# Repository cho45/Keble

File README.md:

# Keble
My Keyboard project

![keyboard]( https://lh3.googleusercontent.com/EfxbqDVbFUMFygQ37cw-t-osZh-F7l7Be6ySQvdsSEX0ixMYkyIdGHLsxJQ2jPK_8Zz_0KA0nsUGFINB1TGCXRP6lfS0WsB-HddwQOFWCWsFthSKxl6NGZ9FwDPpazG6D0C-81J806JqIFrc-be6p1uPMkH3qnAab_ow4JNFFRUdB4O2-49kGolg-Dy7JXoRlwxNpvhNOfnoP4gZtVEllJxjIrvzIPy5hKqrV-IkeFJhrkAK_e5a8ZNKsllVUzNcYYQIi22m2K5YhwaDDLRgU-2dTrrQqDLFtFhZ6oY2y8DjeTC2zXfAGccmpLrrazCjzrdYzKibt8z4t2GqVdgDhCtJQ7x6MYJDr5eFAhxukxrMP_dcSZdACXUI4Rjq47IPYyl1GPYx97pCoO8hBt4gX-3HaJTRLynqYn73mz2nr6UBCkSG0HlI_O6zHuUVOPiS8QQIJsX-bBW7ScQR7BRKUgOtjzX-zlCG5ynrySV1wSH0WuWNiJt9iEEp95V1wKW2NQUl0bESZkWuitu_E9rONg5-YWEImFMoQkPSbXobiScAQ6pdmA8vURFWd6wHuSsA_RqvVRxijmWQiCGAefmiXdKXR_iKclWGiZpoRNCDzVIgeSu1jw=w1756-h748-no )

## Schematic/PCB Project

This is KiCAD project.

Open Root.sch for viewing overall schematic.

## Using Hardwares

 * BLE Nano (nRF51288)
 * MCP23017 (I2C GPIO)
 * Gateron Switches (Cherry MX compatible)

## Firmware

https://developer.mbed.org/users/cho45/code/keyboard/

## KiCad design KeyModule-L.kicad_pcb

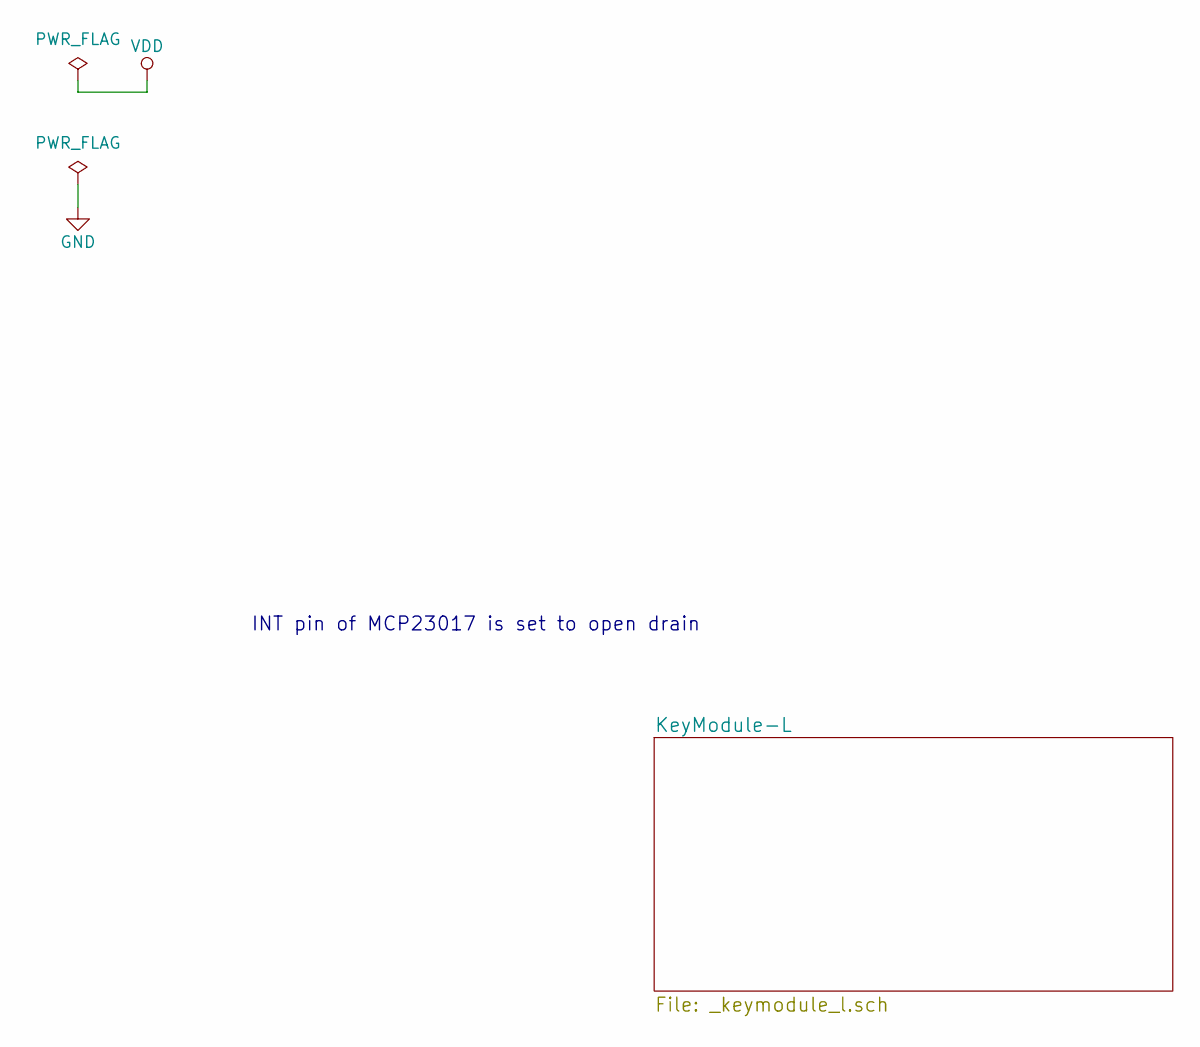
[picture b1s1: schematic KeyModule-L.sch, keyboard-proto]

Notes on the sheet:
INT pin of MCP23017 is set to open drain

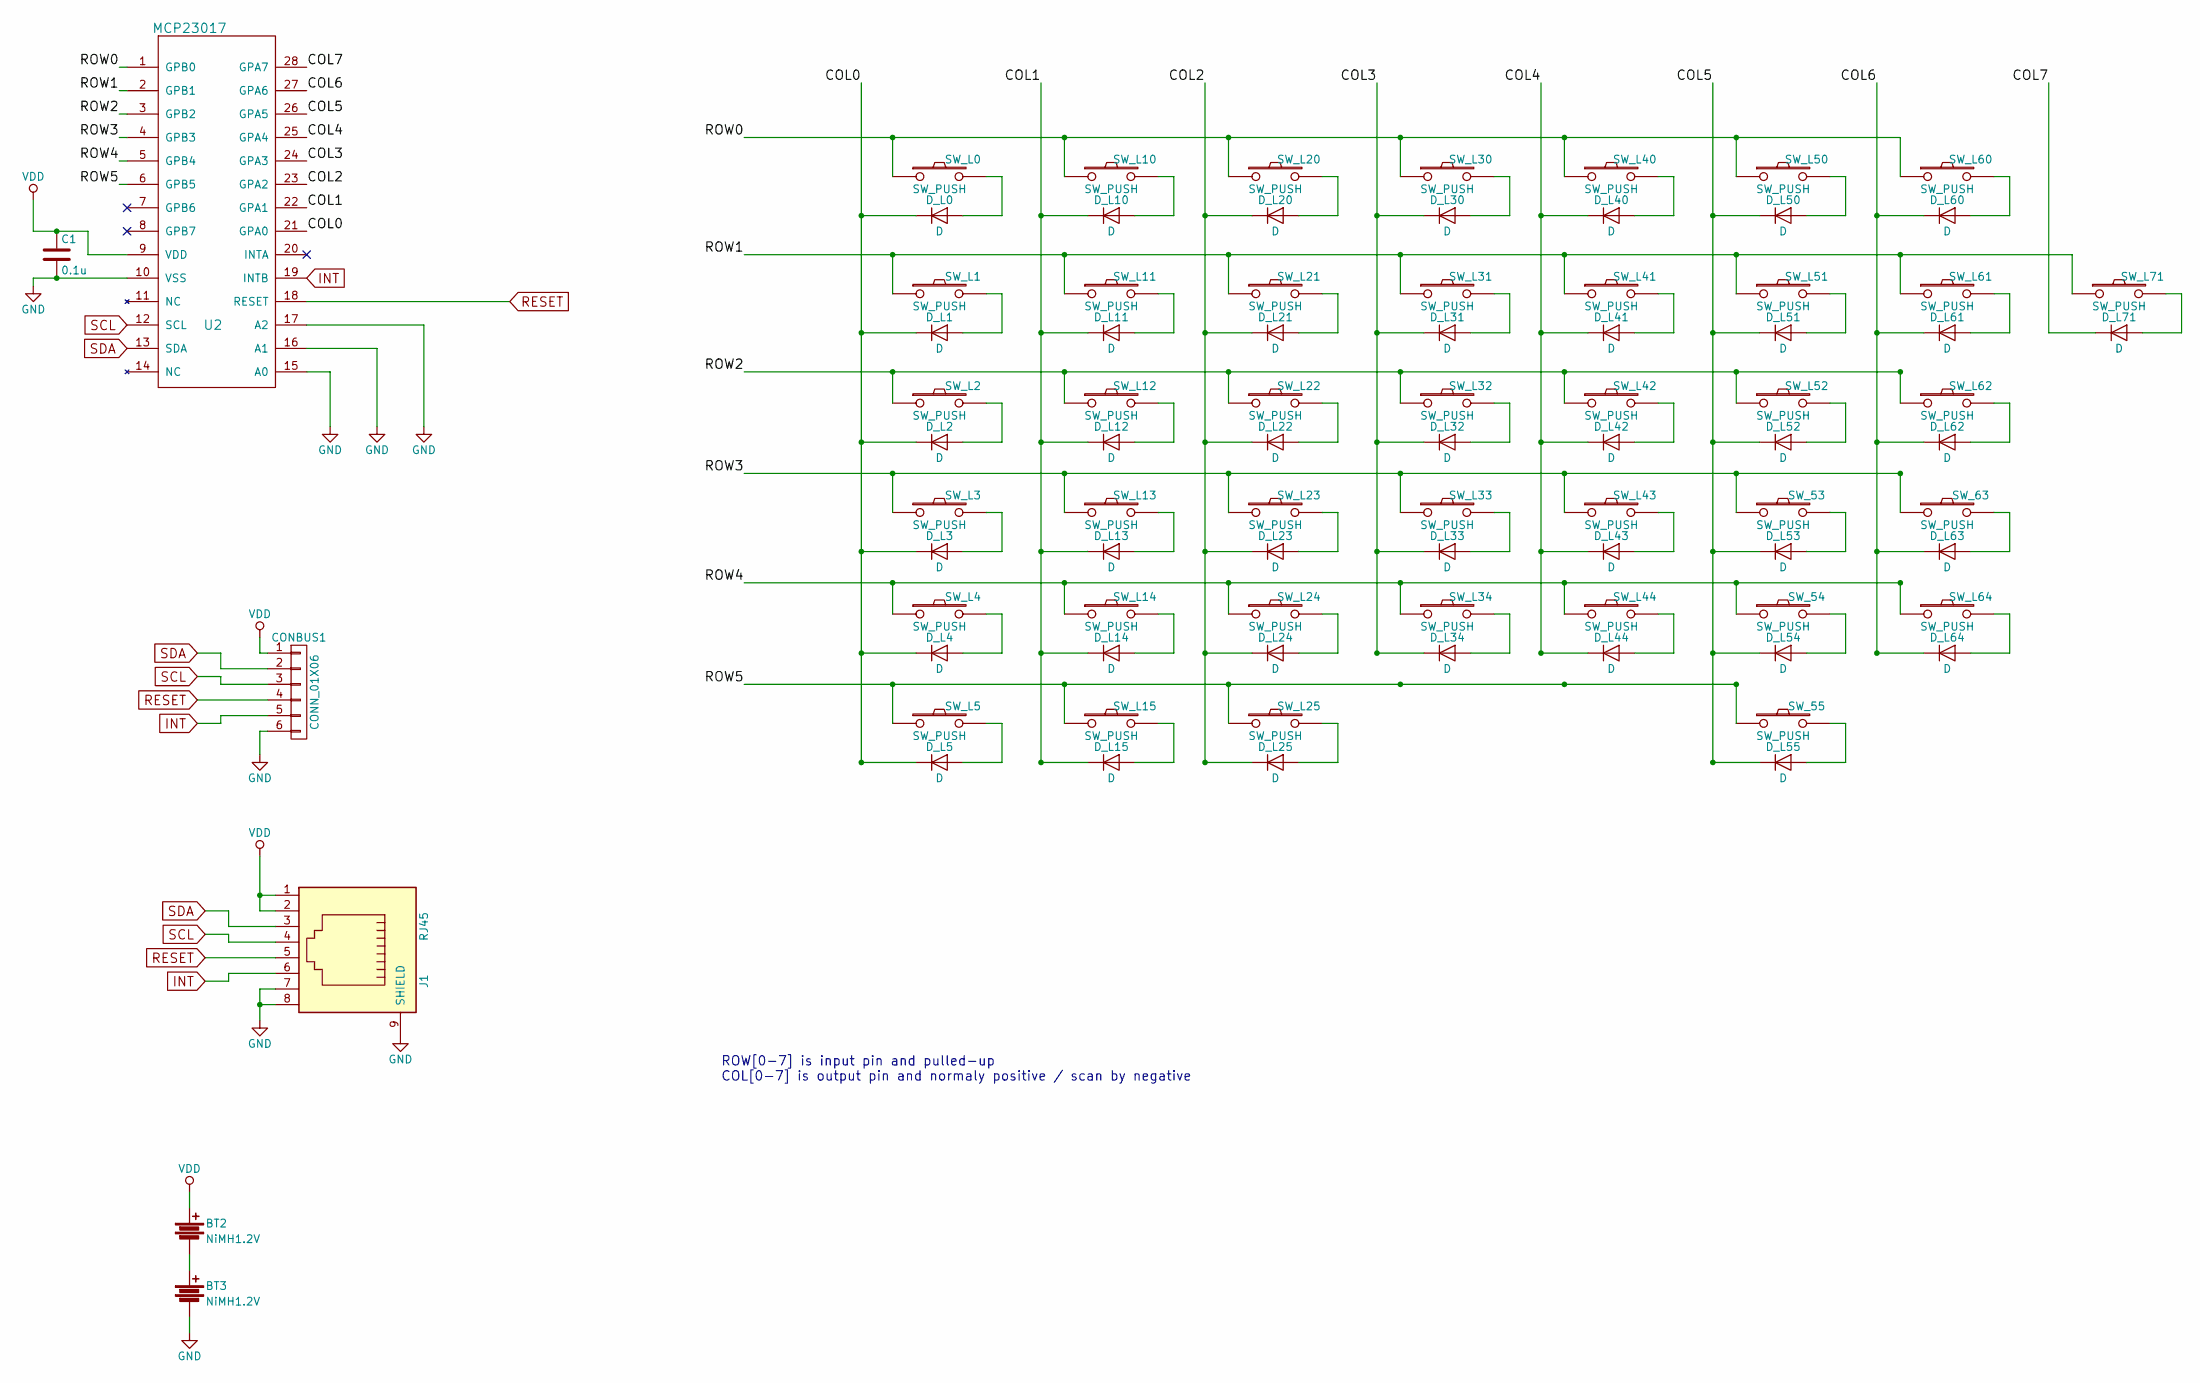
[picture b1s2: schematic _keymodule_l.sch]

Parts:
BT2, BT3: NiMH1.2V; BAT-P-00308
C1: 0.1u; C_Rect_L4_W2.5_P2.5
CONBUS1: CONN_01X06; Socket_Strip_Straight_1x06
D_L0, D_L1, D_L2, D_L3, D_L4, D_L5, D_L10, D_L11, D_L12, D_L13, D_L14, D_L15, D_L20, D_L21, D_L22, D_L23, D_L24, D_L25, D_L30, D_L31, D_L32, D_L33, D_L34, D_L40, D_L41, D_L42, D_L43, D_L44, D_L50, D_L51, D_L52, D_L53, D_L54, D_L55, D_L60, D_L61, D_L62, D_L63, D_L64, D_L71: D; Diode_DO-35_SOD27_Horizontal_RM10
J1: RJ45; RJ45-7810-XPXC
SW_53, SW_54, SW_55, SW_63: SW_PUSH; MX1A
SW_L0, SW_L1, SW_L2, SW_L3, SW_L4, SW_L5, SW_L10, SW_L11, SW_L12, SW_L13, SW_L14, SW_L15, SW_L20, SW_L21, SW_L22, SW_L23, SW_L24, SW_L25, SW_L30, SW_L31, SW_L32, SW_L33, SW_L34, SW_L40, SW_L41, SW_L42, SW_L43, SW_L44, SW_L50, SW_L51, SW_L52, SW_L60, SW_L61, SW_L62, SW_L64, SW_L71: SW_PUSH; MX1A
U3: MCP23017; DIP-28_W7.62mm_LongPads

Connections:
/KeyModule-L/COL0: D_L0.1 (K), D_L1.1 (K), D_L2.1 (K), D_L3.1 (K), D_L4.1 (K), D_L5.1 (K); also elsewhere on the board
/KeyModule-L/COL1: D_L10.1 (K), D_L11.1 (K), D_L12.1 (K), D_L13.1 (K), D_L14.1 (K), D_L15.1 (K); also elsewhere on the board
/KeyModule-L/COL2: D_L20.1 (K), D_L21.1 (K), D_L22.1 (K), D_L23.1 (K), D_L24.1 (K), D_L25.1 (K); also elsewhere on the board
/KeyModule-L/COL3: D_L30.1 (K), D_L31.1 (K), D_L32.1 (K), D_L33.1 (K), D_L34.1 (K); also elsewhere on the board
/KeyModule-L/COL4: D_L40.1 (K), D_L41.1 (K), D_L42.1 (K), D_L43.1 (K), D_L44.1 (K); also elsewhere on the board
/KeyModule-L/COL5: D_L50.1 (K), D_L51.1 (K), D_L52.1 (K), D_L53.1 (K), D_L54.1 (K), D_L55.1 (K); also elsewhere on the board
/KeyModule-L/COL6: D_L60.1 (K), D_L61.1 (K), D_L62.1 (K), D_L63.1 (K), D_L64.1 (K); also elsewhere on the board
/KeyModule-L/COL7: D_L71.1 (K); also elsewhere on the board
/KeyModule-L/ROW0: SW_L0.1, SW_L10.1, SW_L20.1, SW_L30.1, SW_L40.1, SW_L50.1, SW_L60.1; also elsewhere on the board
/KeyModule-L/ROW1: SW_L1.1, SW_L11.1, SW_L21.1, SW_L31.1, SW_L41.1, SW_L51.1, SW_L61.1, SW_L71.1; also elsewhere on the board
/KeyModule-L/ROW2: SW_L2.1, SW_L12.1, SW_L22.1, SW_L32.1, SW_L42.1, SW_L52.1, SW_L62.1; also elsewhere on the board
/KeyModule-L/ROW3: SW_53.1, SW_63.1, SW_L3.1, SW_L13.1, SW_L23.1, SW_L33.1, SW_L43.1; also elsewhere on the board
/KeyModule-L/ROW4: SW_54.1, SW_L4.1, SW_L14.1, SW_L24.1, SW_L34.1, SW_L44.1, SW_L64.1; also elsewhere on the board
/KeyModule-L/ROW5: SW_55.1, SW_L5.1, SW_L15.1, SW_L25.1; also elsewhere on the board
GND: BT3.2, C1.2, CONBUS1.6, J1.7, J1.8, J1.9 (SHIELD); also elsewhere on the board
INT: CONBUS1.5, J1.6; also elsewhere on the board
unnamed: BT2.2, BT3.1
unnamed: D_L0.2 (A), SW_L0.2
unnamed: D_L1.2 (A), SW_L1.2
unnamed: D_L2.2 (A), SW_L2.2
unnamed: D_L3.2 (A), SW_L3.2
unnamed: D_L4.2 (A), SW_L4.2
unnamed: D_L5.2 (A), SW_L5.2
unnamed: D_L10.2 (A), SW_L10.2
unnamed: D_L11.2 (A), SW_L11.2
unnamed: D_L12.2 (A), SW_L12.2
unnamed: D_L13.2 (A), SW_L13.2
unnamed: D_L14.2 (A), SW_L14.2
unnamed: D_L15.2 (A), SW_L15.2
unnamed: D_L20.2 (A), SW_L20.2
unnamed: D_L21.2 (A), SW_L21.2
unnamed: D_L22.2 (A), SW_L22.2
unnamed: D_L23.2 (A), SW_L23.2
unnamed: D_L24.2 (A), SW_L24.2
unnamed: D_L25.2 (A), SW_L25.2
unnamed: D_L30.2 (A), SW_L30.2
unnamed: D_L31.2 (A), SW_L31.2
unnamed: D_L32.2 (A), SW_L32.2
unnamed: D_L33.2 (A), SW_L33.2
unnamed: D_L34.2 (A), SW_L34.2
unnamed: D_L40.2 (A), SW_L40.2
unnamed: D_L41.2 (A), SW_L41.2
unnamed: D_L42.2 (A), SW_L42.2
unnamed: D_L43.2 (A), SW_L43.2
unnamed: D_L44.2 (A), SW_L44.2
unnamed: D_L50.2 (A), SW_L50.2
unnamed: D_L51.2 (A), SW_L51.2
unnamed: D_L52.2 (A), SW_L52.2
unnamed: D_L53.2 (A), SW_53.2
unnamed: D_L54.2 (A), SW_54.2
unnamed: D_L55.2 (A), SW_55.2
unnamed: D_L60.2 (A), SW_L60.2
unnamed: D_L61.2 (A), SW_L61.2
unnamed: D_L62.2 (A), SW_L62.2
unnamed: D_L63.2 (A), SW_63.2
unnamed: D_L64.2 (A), SW_L64.2
unnamed: D_L71.2 (A), SW_L71.2
RESET: CONBUS1.4, J1.5; also elsewhere on the board
SCL: CONBUS1.3, J1.4; also elsewhere on the board
SDA: CONBUS1.2, J1.3; also elsewhere on the board
VDD: BT2.1, C1.1, CONBUS1.1, J1.1, J1.2; also elsewhere on the board

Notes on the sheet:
ROW[0-7] is input pin and pulled-up COL[0-7] is output pin and normaly positive / scan by negative

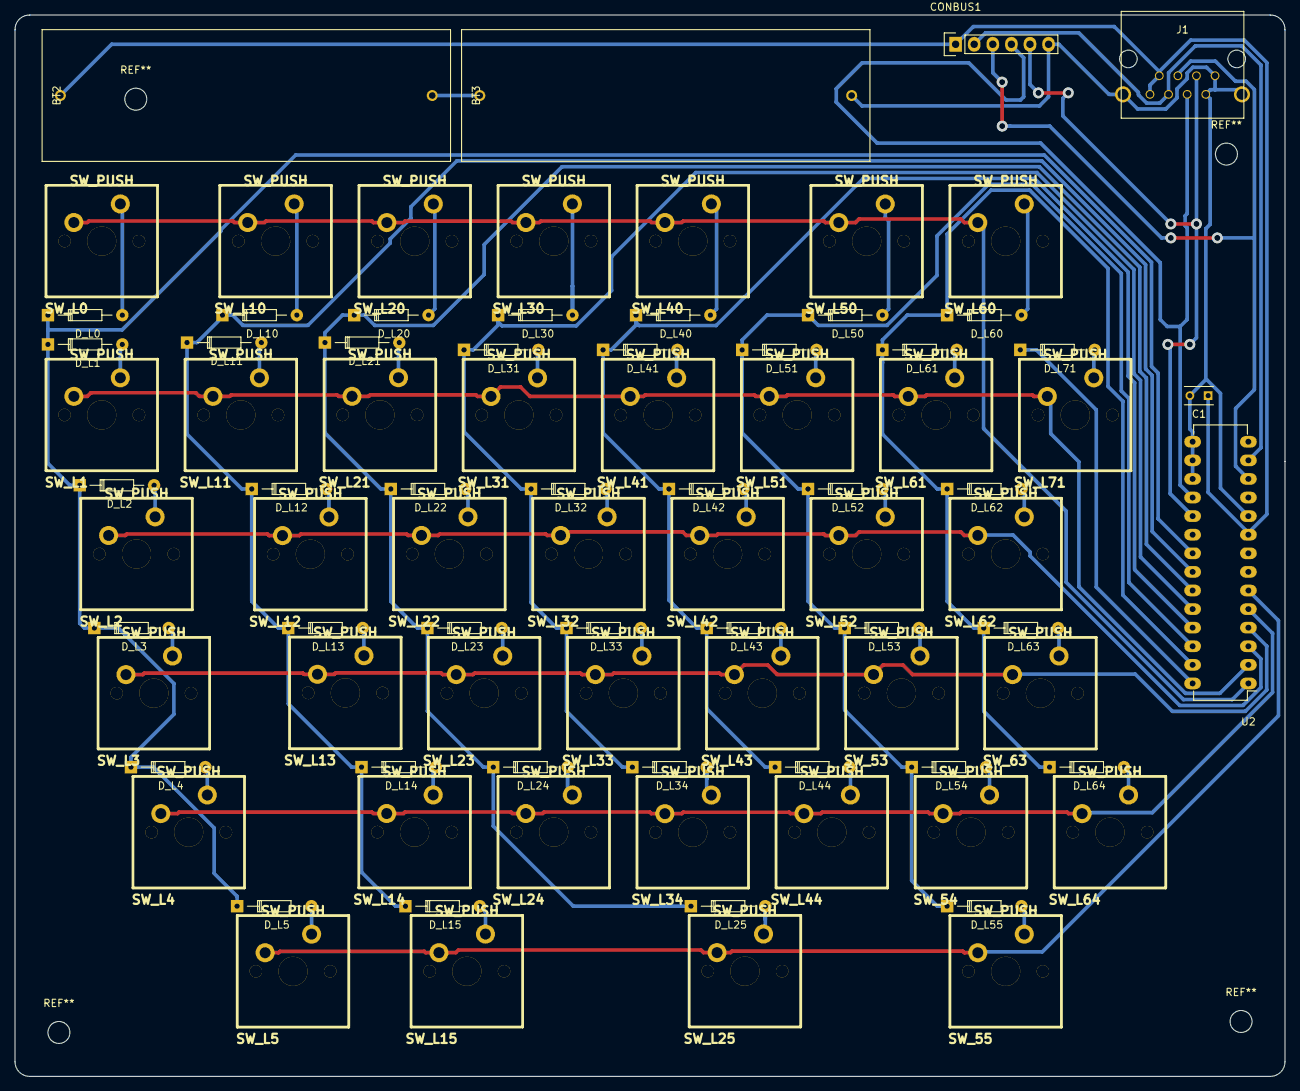
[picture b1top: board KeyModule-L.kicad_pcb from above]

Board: 2 copper layers, 173.5 x 145.0 mm, 86 parts (0 on the bottom side), 61 nets.

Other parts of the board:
U2: MCP23017; DIP-28_W7.62mm_LongPads

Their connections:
/KeyModule-L/COL0: U2.21; also elsewhere on the board
/KeyModule-L/COL1: U2.22; also elsewhere on the board
/KeyModule-L/COL2: U2.23; also elsewhere on the board
/KeyModule-L/COL3: U2.24; also elsewhere on the board
/KeyModule-L/COL4: U2.25; also elsewhere on the board
/KeyModule-L/COL5: U2.26; also elsewhere on the board
/KeyModule-L/COL6: U2.27; also elsewhere on the board
/KeyModule-L/COL7: U2.28; also elsewhere on the board
/KeyModule-L/ROW0: U2.1; also elsewhere on the board
/KeyModule-L/ROW1: U2.2; also elsewhere on the board
/KeyModule-L/ROW2: U2.3; also elsewhere on the board
/KeyModule-L/ROW3: U2.4; also elsewhere on the board
/KeyModule-L/ROW4: U2.5; also elsewhere on the board
/KeyModule-L/ROW5: U2.6; also elsewhere on the board
GND: U2.10, U2.15, U2.16, U2.17; also elsewhere on the board
INT: U2.19; also elsewhere on the board
RESET: U2.18; also elsewhere on the board
SCL: U2.12; also elsewhere on the board
SDA: U2.13; also elsewhere on the board
VDD: U2.9; also elsewhere on the board

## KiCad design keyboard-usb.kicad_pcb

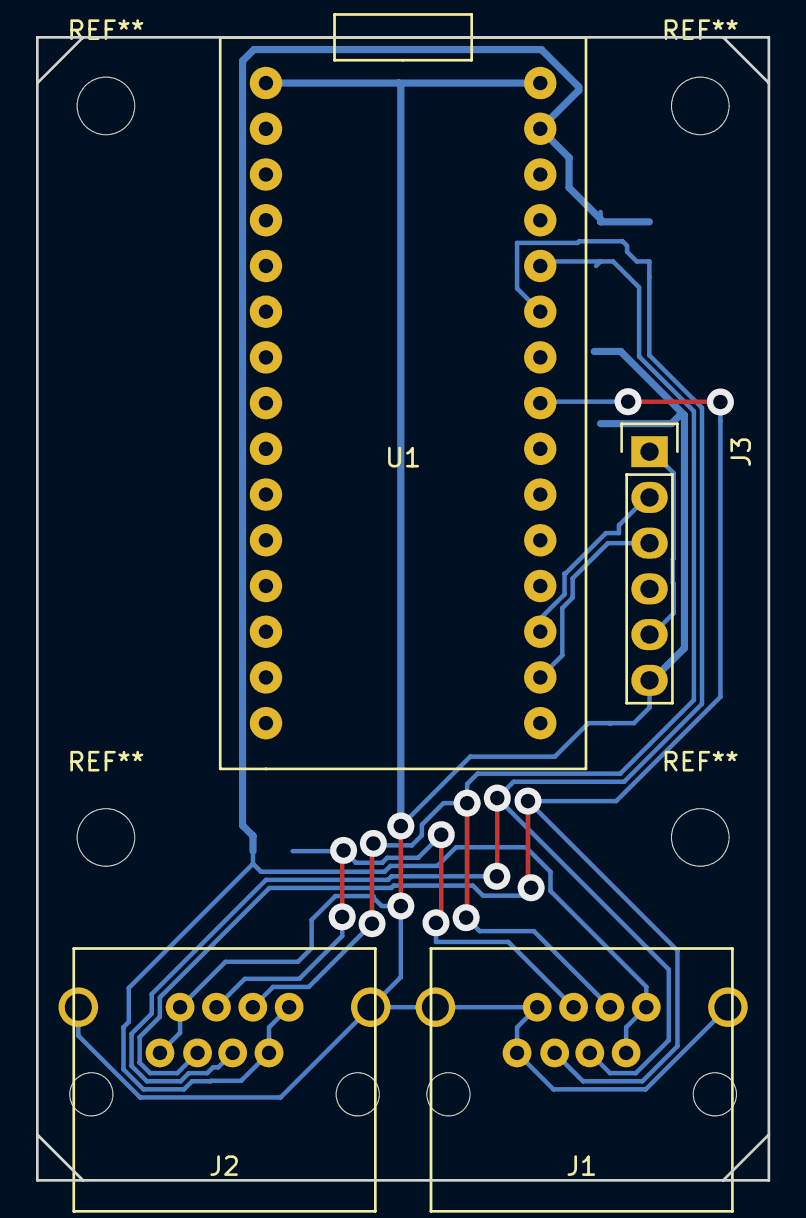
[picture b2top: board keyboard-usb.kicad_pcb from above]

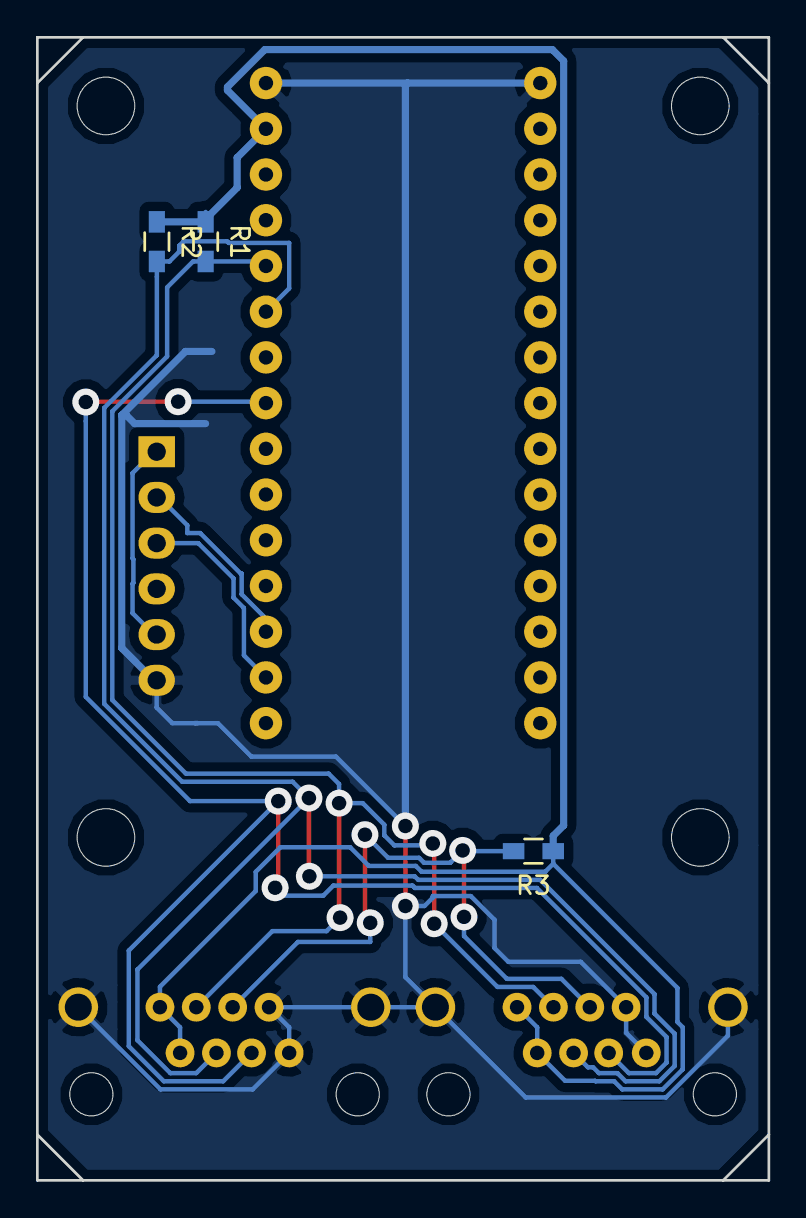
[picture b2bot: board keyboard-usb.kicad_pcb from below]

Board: 2 copper layers, 40.6 x 63.5 mm, 7 parts (3 on the bottom side), 9 nets.

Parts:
J1, J2: RJ45; RJ45-7810-XPXC
J3: Serial; Socket_Strip_Straight_1x06
R1, R2, R3: 2k; R_0603_HandSoldering
U1: LPC11U35-QUICKSTART-BOARD

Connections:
GND: J1.7, J1.8, J1.9, J2.7, J2.8, J2.9, J3.6, U1.1, U1.30
INT: J1.6, J2.6, U1.23
unnamed: J3.1, J3.5
unnamed: J3.2, U1.18
unnamed: J3.3, U1.17
RESET: J1.5, J2.5, R3.2
SCL: J1.4, J2.4, R2.2, U1.25
SDA: J1.3, J2.3, R1.2, U1.26
VDD: J1.1, J1.2, J2.1, J2.2, R1.1, R2.1, R3.1, U1.29

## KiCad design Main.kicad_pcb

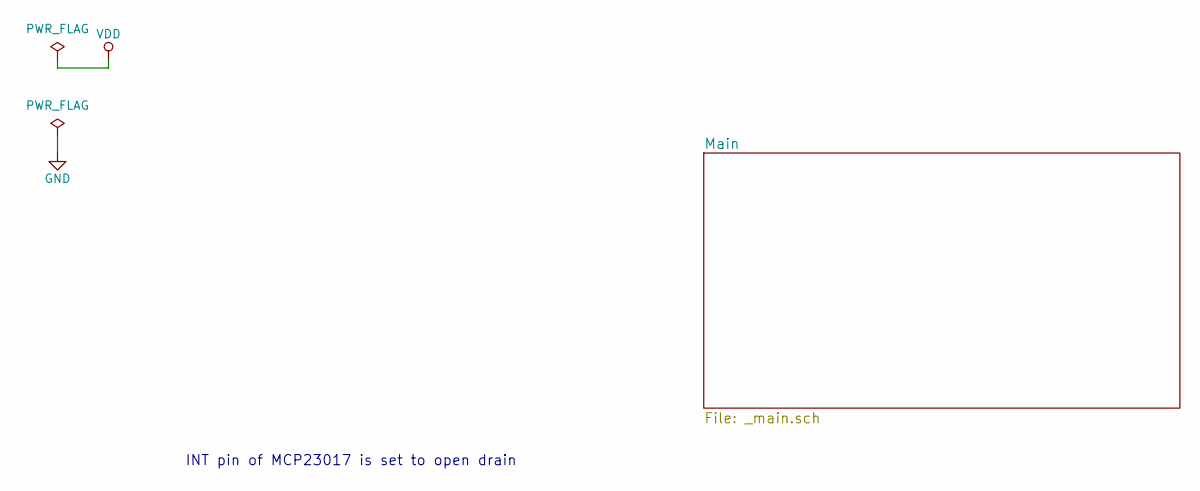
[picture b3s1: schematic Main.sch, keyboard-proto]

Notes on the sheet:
INT pin of MCP23017 is set to open drain

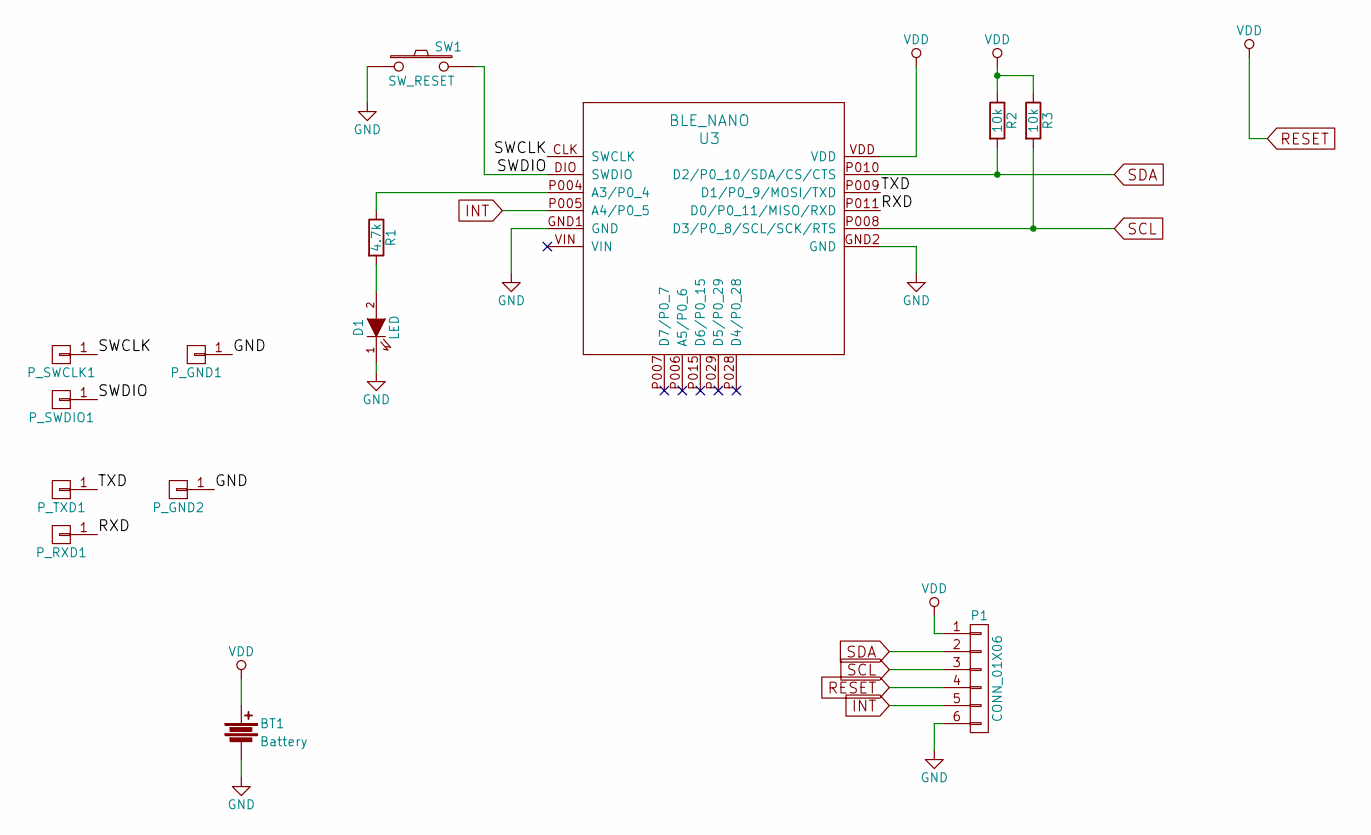
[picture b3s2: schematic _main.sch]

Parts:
BT1: Battery; Pin_Header_Straight_1x02
D1: LED; LED-3MM
P1: CONN_01X06; Pin_Header_Straight_1x06
P_GND1, P_GND2: CONN_01X01; Socket_Strip_Straight_1x01
P_RXD1: CONN_01X01; Socket_Strip_Straight_1x01
P_SWCLK1: CONN_01X01; Socket_Strip_Straight_1x01
P_SWDIO1: CONN_01X01; Socket_Strip_Straight_1x01
P_TXD1: CONN_01X01; Socket_Strip_Straight_1x01
R1: 4.7k; Resistor_Horizontal_RM7mm
R2, R3: 10k; Resistor_Horizontal_RM7mm
SW1: SW_RESET; SW_PUSH-12mm
U3: BLE_NANO

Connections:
/Main/RXD: P_RXD1.1, U3.P011 (D0/P0_11/MISO/RXD)
/Main/SWCLK: P_SWCLK1.1, U3.CLK (SWCLK)
/Main/SWDIO: P_SWDIO1.1, SW1.2, U3.DIO (SWDIO)
/Main/TXD: P_TXD1.1, U3.P009 (D1/P0_9/MOSI/TXD)
GND: BT1.2, D1.1 (K), P1.6, P_GND1.1, P_GND2.1, SW1.1, U3.GND1 (GND), U3.GND2 (GND)
INT: P1.5, U3.P005 (A4/P0_5)
unnamed: D1.2 (A), R1.2
unnamed: R1.1, U3.P004 (A3/P0_4)
RESET: BT1.1, P1.1, P1.4, R2.1, R3.1, U3.VDD
SCL: P1.3, R3.2, U3.P008 (D3/P0_8/SCL/SCK/RTS)
SDA: P1.2, R2.2, U3.P010 (D2/P0_10/SDA/CS/CTS)

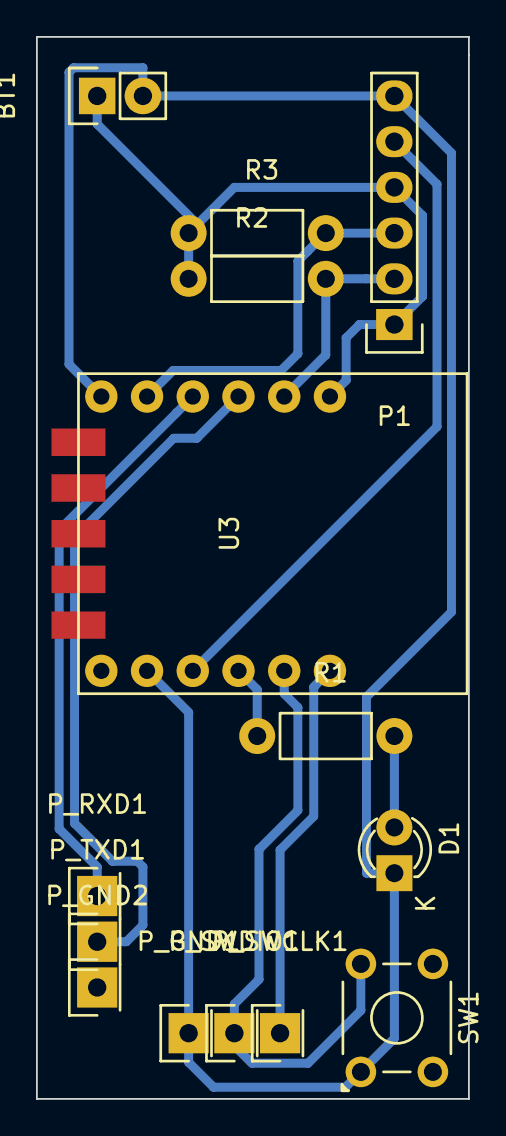
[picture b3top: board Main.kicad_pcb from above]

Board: 2 copper layers, 24.0 x 59.0 mm, 14 parts (0 on the bottom side), 11 nets.

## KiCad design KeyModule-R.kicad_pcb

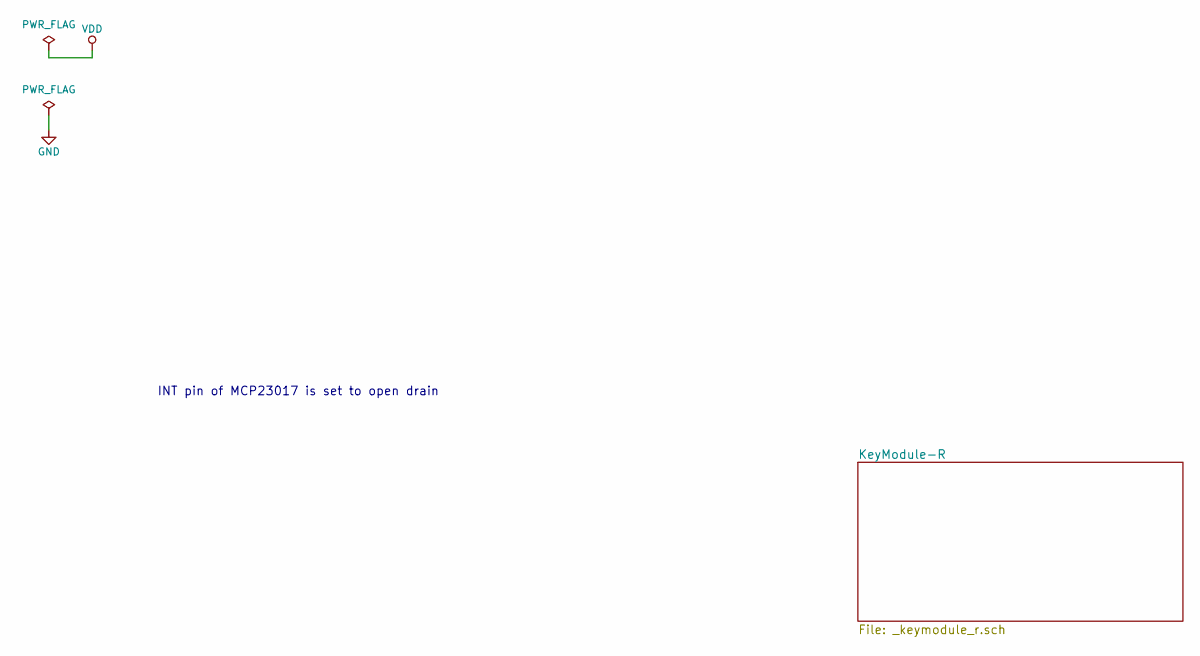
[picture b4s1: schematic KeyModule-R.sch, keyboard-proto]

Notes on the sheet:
INT pin of MCP23017 is set to open drain

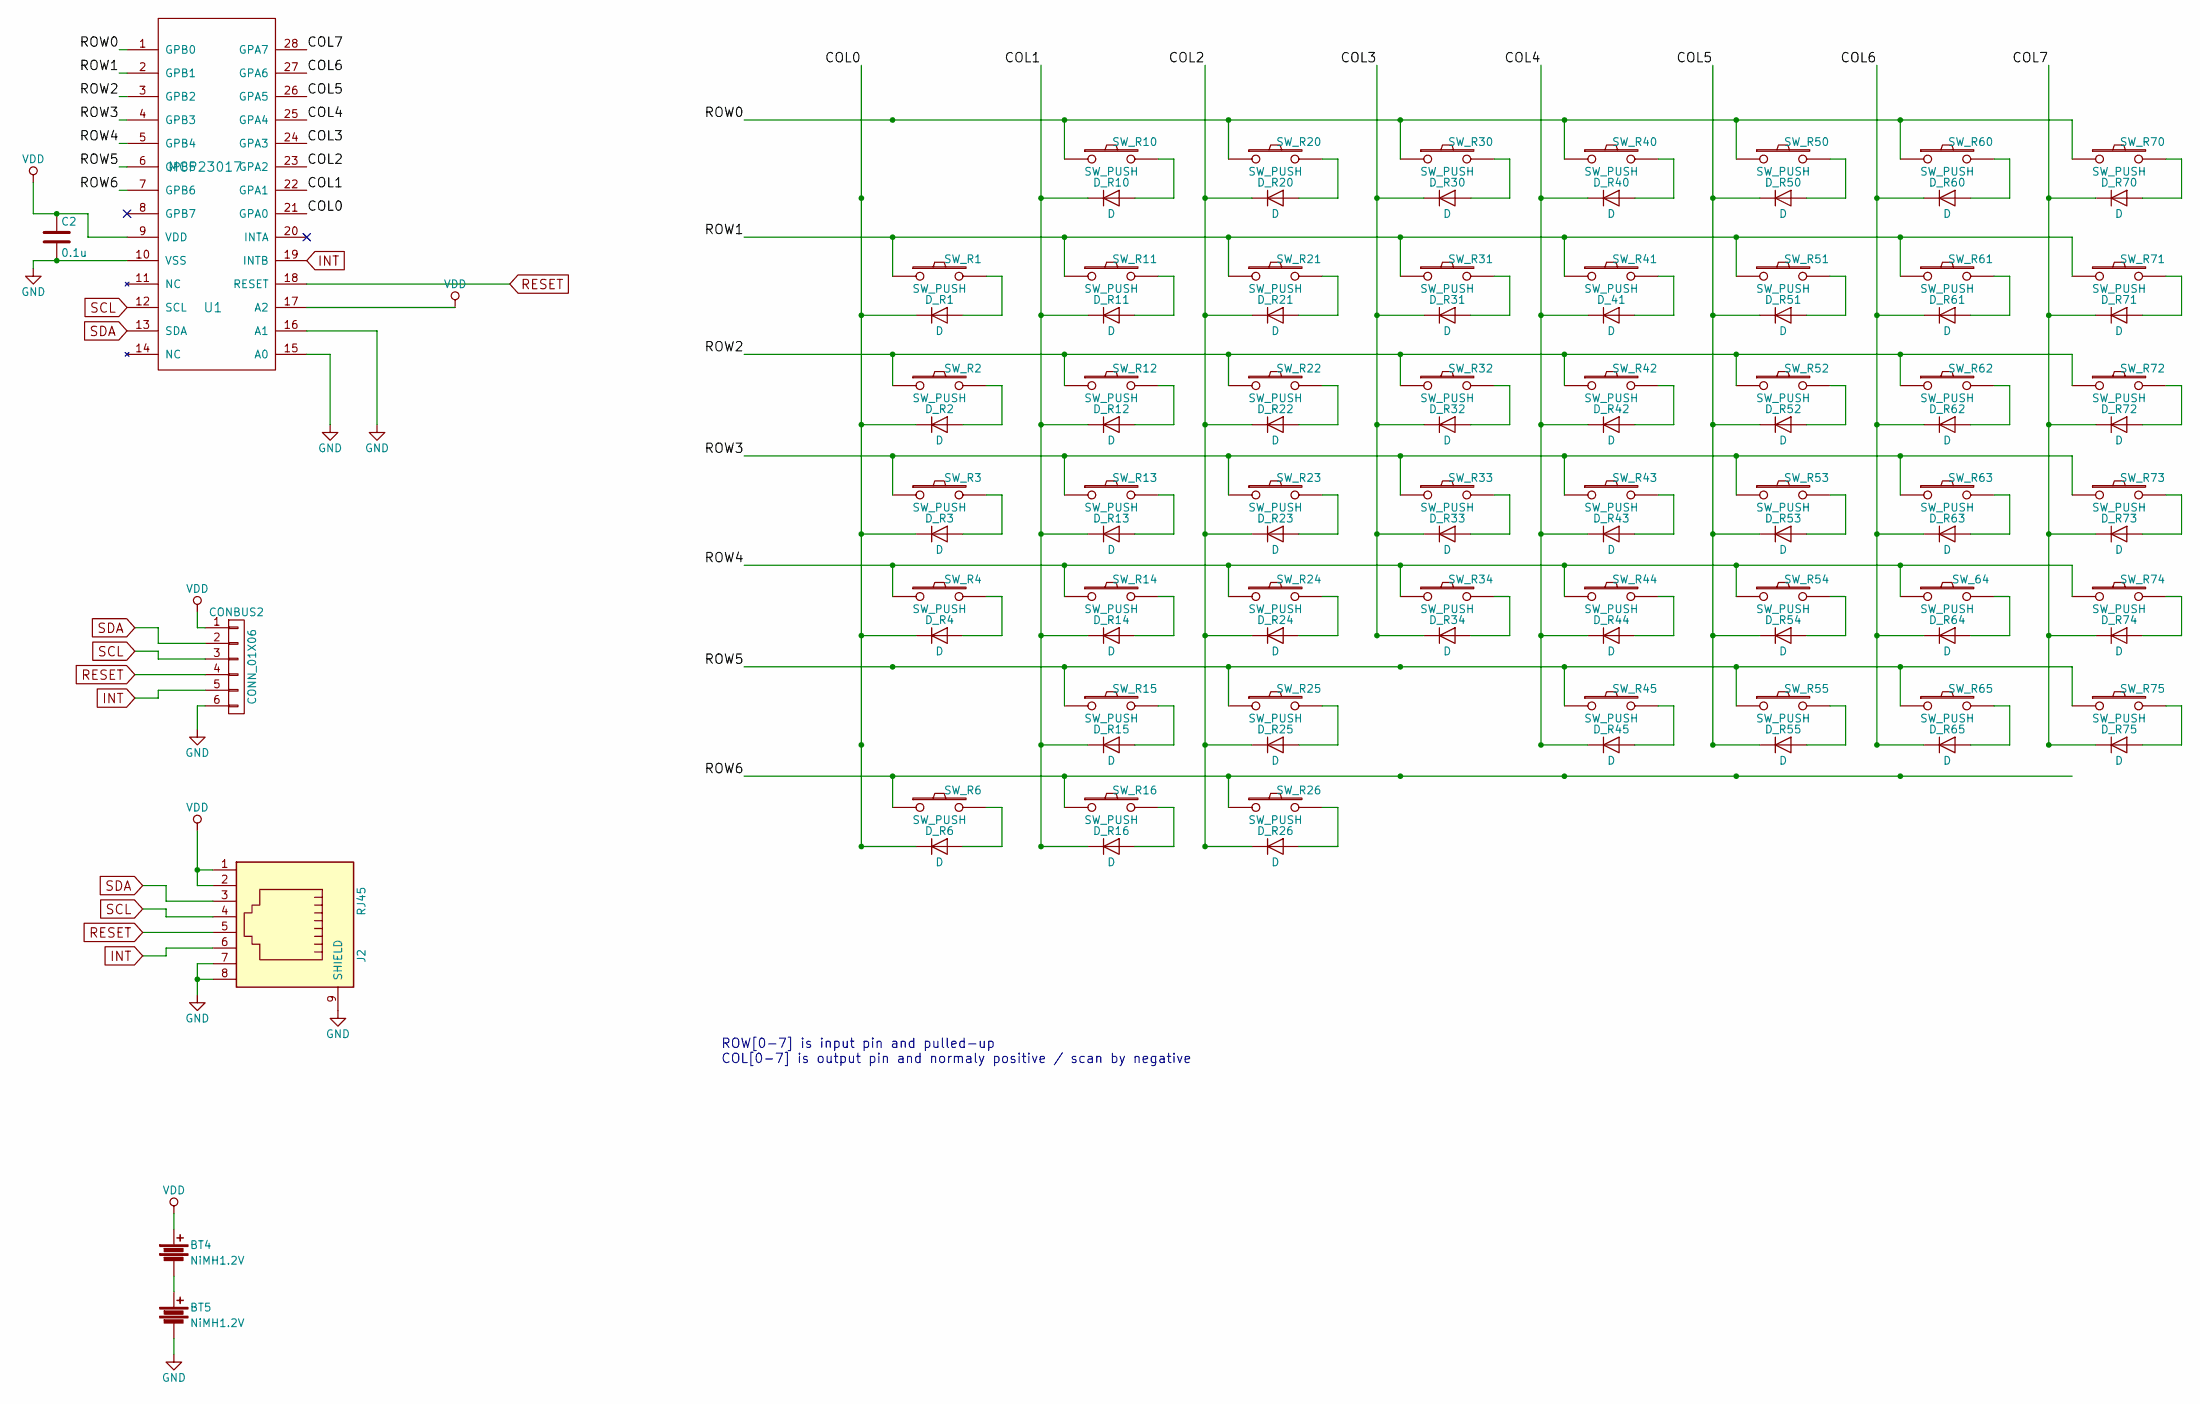
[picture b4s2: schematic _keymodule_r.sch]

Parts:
BT4, BT5: NiMH1.2V; BAT-P-00308
C2: 0.1u; C_Rect_L4_W2.5_P2.5
CONBUS2: CONN_01X06; Socket_Strip_Straight_1x06
D_41: D; Diode_DO-35_SOD27_Horizontal_RM10
D_R1, D_R2, D_R3, D_R4, D_R6, D_R10, D_R11, D_R12, D_R13, D_R14, D_R15, D_R16, D_R20, D_R21, D_R22, D_R23, D_R24, D_R25, D_R26, D_R30, D_R31, D_R32, D_R33, D_R34, D_R40, D_R42, D_R43, D_R44, D_R45, D_R50, D_R51, D_R52, D_R53, D_R54, D_R55, D_R60, D_R61, D_R62, D_R63, D_R64, D_R65, D_R70, D_R71, D_R72, D_R73, D_R74, D_R75: D; Diode_DO-35_SOD27_Horizontal_RM10
J2: RJ45; RJ45-7810-XPXC
SW_64: SW_PUSH; MX1A
SW_R1, SW_R2, SW_R3, SW_R4, SW_R6, SW_R10, SW_R11, SW_R12, SW_R13, SW_R14, SW_R15, SW_R16, SW_R20, SW_R21, SW_R22, SW_R23, SW_R24, SW_R25, SW_R26, SW_R30, SW_R31, SW_R32, SW_R33, SW_R34, SW_R40, SW_R41, SW_R42, SW_R43, SW_R44, SW_R45, SW_R50, SW_R51, SW_R52, SW_R53, SW_R54, SW_R55, SW_R60, SW_R61, SW_R62, SW_R63, SW_R65, SW_R70, SW_R71, SW_R72, SW_R73, SW_R74, SW_R75: SW_PUSH; MX1A
U1: MCP23017; DIP-28_W7.62mm_LongPads

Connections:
/KeyModule-R/COL0: D_R1.1 (K), D_R2.1 (K), D_R3.1 (K), D_R4.1 (K), D_R6.1 (K), U1.21 (GPA0)
/KeyModule-R/COL1: D_R10.1 (K), D_R11.1 (K), D_R12.1 (K), D_R13.1 (K), D_R14.1 (K), D_R15.1 (K), D_R16.1 (K), U1.22 (GPA1)
/KeyModule-R/COL2: D_R20.1 (K), D_R21.1 (K), D_R22.1 (K), D_R23.1 (K), D_R24.1 (K), D_R25.1 (K), D_R26.1 (K), U1.23 (GPA2)
/KeyModule-R/COL3: D_R30.1 (K), D_R31.1 (K), D_R32.1 (K), D_R33.1 (K), D_R34.1 (K), U1.24 (GPA3)
/KeyModule-R/COL4: D_41.1 (K), D_R40.1 (K), D_R42.1 (K), D_R43.1 (K), D_R44.1 (K), D_R45.1 (K), U1.25 (GPA4)
/KeyModule-R/COL5: D_R50.1 (K), D_R51.1 (K), D_R52.1 (K), D_R53.1 (K), D_R54.1 (K), D_R55.1 (K), U1.26 (GPA5)
/KeyModule-R/COL6: D_R60.1 (K), D_R61.1 (K), D_R62.1 (K), D_R63.1 (K), D_R64.1 (K), D_R65.1 (K), U1.27 (GPA6)
/KeyModule-R/COL7: D_R70.1 (K), D_R71.1 (K), D_R72.1 (K), D_R73.1 (K), D_R74.1 (K), D_R75.1 (K), U1.28 (GPA7)
/KeyModule-R/ROW0: SW_R10.1, SW_R20.1, SW_R30.1, SW_R40.1, SW_R50.1, SW_R60.1, SW_R70.1, U1.1 (GPB0)
/KeyModule-R/ROW1: SW_R1.1, SW_R11.1, SW_R21.1, SW_R31.1, SW_R41.1, SW_R51.1, SW_R61.1, SW_R71.1, U1.2 (GPB1)
/KeyModule-R/ROW2: SW_R2.1, SW_R12.1, SW_R22.1, SW_R32.1, SW_R42.1, SW_R52.1, SW_R62.1, SW_R72.1, U1.3 (GPB2)
/KeyModule-R/ROW3: SW_R3.1, SW_R13.1, SW_R23.1, SW_R33.1, SW_R43.1, SW_R53.1, SW_R63.1, SW_R73.1, U1.4 (GPB3)
/KeyModule-R/ROW4: SW_64.1, SW_R4.1, SW_R14.1, SW_R24.1, SW_R34.1, SW_R44.1, SW_R54.1, SW_R74.1, U1.5 (GPB4)
/KeyModule-R/ROW5: SW_R15.1, SW_R25.1, SW_R45.1, SW_R55.1, SW_R65.1, SW_R75.1, U1.6 (GPB5)
/KeyModule-R/ROW6: SW_R6.1, SW_R16.1, SW_R26.1, U1.7 (GPB6)
GND: BT5.2, C2.2, CONBUS2.6, J2.7, J2.8, J2.9 (SHIELD), U1.10 (VSS), U1.15 (A0), U1.16 (A1)
INT: CONBUS2.5, J2.6, U1.19 (INTB)
unnamed: BT4.2, BT5.1
unnamed: D_41.2 (A), SW_R41.2
unnamed: D_R1.2 (A), SW_R1.2
unnamed: D_R2.2 (A), SW_R2.2
unnamed: D_R3.2 (A), SW_R3.2
unnamed: D_R4.2 (A), SW_R4.2
unnamed: D_R6.2 (A), SW_R6.2
unnamed: D_R10.2 (A), SW_R10.2
unnamed: D_R11.2 (A), SW_R11.2
unnamed: D_R12.2 (A), SW_R12.2
unnamed: D_R13.2 (A), SW_R13.2
unnamed: D_R14.2 (A), SW_R14.2
unnamed: D_R15.2 (A), SW_R15.2
unnamed: D_R16.2 (A), SW_R16.2
unnamed: D_R20.2 (A), SW_R20.2
unnamed: D_R21.2 (A), SW_R21.2
unnamed: D_R22.2 (A), SW_R22.2
unnamed: D_R23.2 (A), SW_R23.2
unnamed: D_R24.2 (A), SW_R24.2
unnamed: D_R25.2 (A), SW_R25.2
unnamed: D_R26.2 (A), SW_R26.2
unnamed: D_R30.2 (A), SW_R30.2
unnamed: D_R31.2 (A), SW_R31.2
unnamed: D_R32.2 (A), SW_R32.2
unnamed: D_R33.2 (A), SW_R33.2
unnamed: D_R34.2 (A), SW_R34.2
unnamed: D_R40.2 (A), SW_R40.2
unnamed: D_R42.2 (A), SW_R42.2
unnamed: D_R43.2 (A), SW_R43.2
unnamed: D_R44.2 (A), SW_R44.2
unnamed: D_R45.2 (A), SW_R45.2
unnamed: D_R50.2 (A), SW_R50.2
unnamed: D_R51.2 (A), SW_R51.2
unnamed: D_R52.2 (A), SW_R52.2
unnamed: D_R53.2 (A), SW_R53.2
unnamed: D_R54.2 (A), SW_R54.2
unnamed: D_R55.2 (A), SW_R55.2
unnamed: D_R60.2 (A), SW_R60.2
unnamed: D_R61.2 (A), SW_R61.2
unnamed: D_R62.2 (A), SW_R62.2
unnamed: D_R63.2 (A), SW_R63.2
unnamed: D_R64.2 (A), SW_64.2
unnamed: D_R65.2 (A), SW_R65.2
unnamed: D_R70.2 (A), SW_R70.2
unnamed: D_R71.2 (A), SW_R71.2
unnamed: D_R72.2 (A), SW_R72.2
unnamed: D_R73.2 (A), SW_R73.2
unnamed: D_R74.2 (A), SW_R74.2
unnamed: D_R75.2 (A), SW_R75.2
RESET: CONBUS2.4, J2.5, U1.18 (RESET)
SCL: CONBUS2.3, J2.4, U1.12 (SCL)
SDA: CONBUS2.2, J2.3, U1.13 (SDA)
VDD: BT4.1, C2.1, CONBUS2.1, J2.1, J2.2, U1.9 (VDD), U1.17 (A2)

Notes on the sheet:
ROW[0-7] is input pin and pulled-up COL[0-7] is output pin and normaly positive / scan by negative

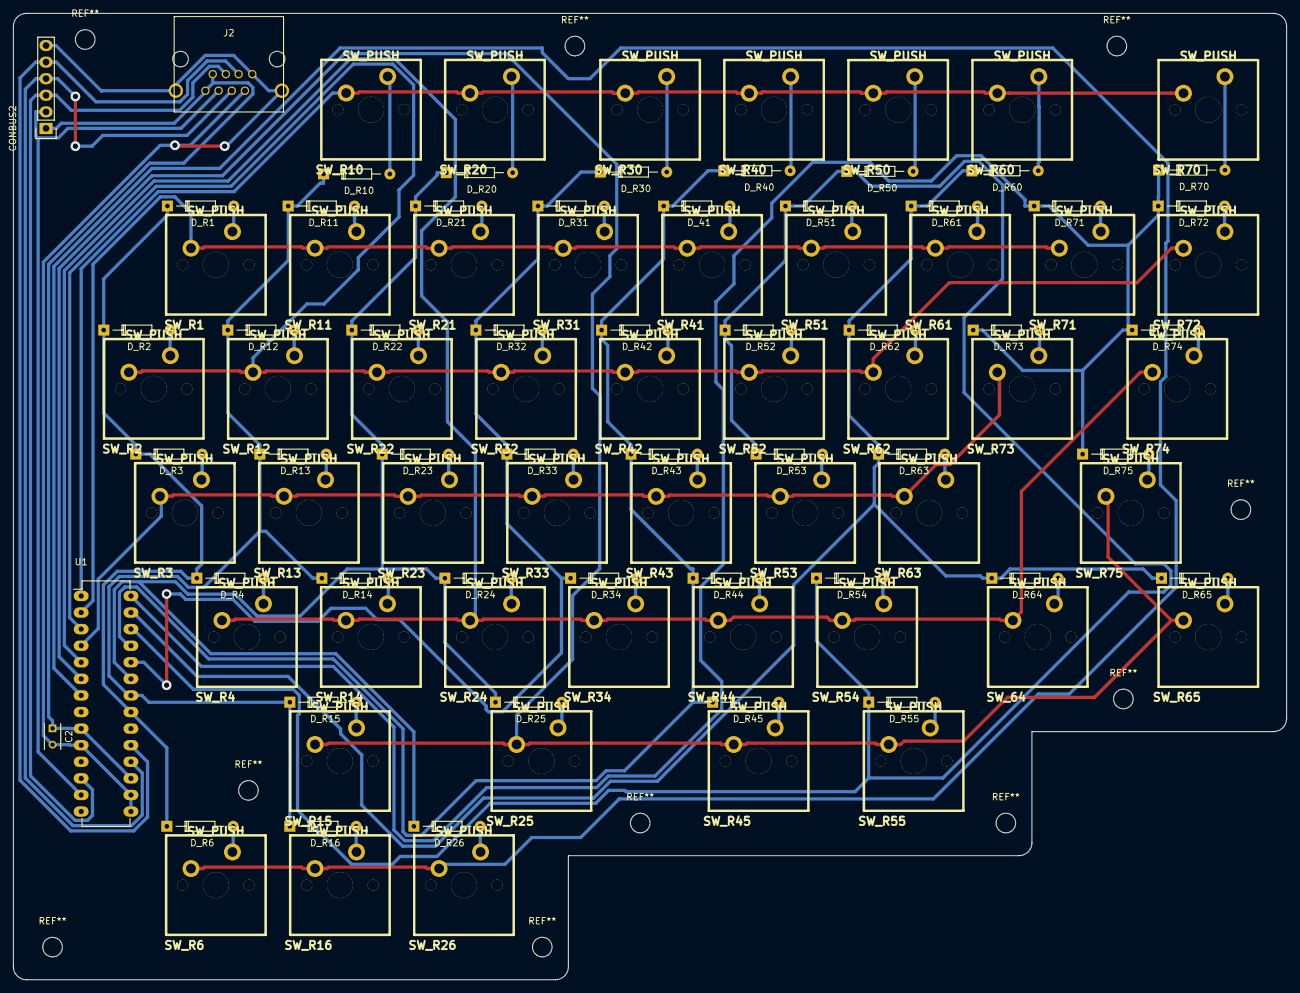
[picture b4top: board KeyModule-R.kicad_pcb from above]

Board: 2 copper layers, 195.0 x 148.0 mm, 100 parts (0 on the bottom side), 69 nets.

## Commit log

2016-07-25 init
2016-07-25 append modules
2016-07-25 footprint
